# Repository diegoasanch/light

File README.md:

# Light

A WiFi-enabled LED light controller, based on the [RP2350](https://www.raspberrypi.com/products/rp2350/).

You can view the [PCB and schematics online here](https://kicanvas.org/?github=https://github.com/diegoasanch/light/blob/main/v1/kicad/light.kicad_pro).

<div align="center">

</div>

## What you'll see here

| File type                                     | Status        |
| --------------------------------------------- | -----------   |
| KiCad design files for the schematics and PCB | ✅             |
| Firmware source code                          | 🏗️ in progress |
| Interactive 3D PCB viewer (`web/`)            | ✅             |
| Frontend source code                          | -             |
| 3D models for the enclosure                   | -             |

> [!WARNING]
> This project is still under development.

## Why

I'm currently leveling up my electronics skills and learning about PCB design; I did a [similar (albeit much more simple) project](https://github.com/diegoasanch/RGB-Controller) in the past, so since I'm already familiar with the concepts I thought it would be a good starter project into the world of PCBs.

---

# Project structre

<div align="center">
  
</div>

## PCB

KiCad project, located in `./v1/kicad/` contains all of the designs and BOM

## Firmware

Cargo project using embassy-rs `./v1/firmware/`

## Web viewer

Interactive three.js render of the board built from the real KiCad data —
every copper layer, dielectric slab, mask, silkscreen and via as separate
toggleable 3D elements, with an exploded view. Lives in `./web/`
(`pnpm dev`); regenerate its data from the board file with `pnpm sync-pcb`.

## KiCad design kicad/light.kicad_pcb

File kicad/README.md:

# Configuring KiCad

No configuration needed: all project symbols, footprints and 3D models live in
`kicad/libs/` and are referenced via the built-in `${KIPRJMOD}` variable
(the directory containing the project file), so a fresh clone renders the full
3D board out of the box.

> Historical note: the project previously required a manually configured
> `LIGHT_PROJECT_LIB_DIR` path variable (`Preferences > Configure Paths...`).
> That was replaced with `${KIPRJMOD}/libs` in 2026-08 — if your KiCad still
> has the old variable defined, it is unused and can be deleted.

Stock-library models are referenced through `${KICAD9_3DMODEL_DIR}`; KiCad 10
resolves the legacy variable to its own model directory automatically (the
`.wrl` references resolve to the shipped `.step` files).

## 3D model sources

- `libs/RP2350_KiCad/` — symbol, footprint and STEP for the RP2350A from
  [HDR/RP2350_KiCad](https://github.com/HDR/RP2350_KiCad) (GPL-3.0, LICENSE
  included in the directory).
- `libs/GT-EVA01AA-L1.pretty/` — rotary encoder (G-Switch GT-EVA01AA-L1,
  LCSC C17702124) WRL/STEP fetched from the EasyEDA parts API via
  `easyeda2kicad`. The WRL is referenced by the board; the same-basename STEP
  is there for `kicad-cli pcb export step/glb --subst-models`. The raw
  EasyEDA STEP sits 0.9741 mm off the WRL in Y, so the committed STEP has the
  origin of its root `AXIS2_PLACEMENT_3D` (entity `#15348`) shifted by that
  amount — shifting the `CARTESIAN_POINT`s instead gets applied twice by the
  OCC import chain, and any edit must round-trip the file byte-exactly
  (an earlier encoding-damaged copy made OCC import it as empty geometry).
  Verified via `web/scripts/sync-pcb.ts`'s GLB export: model bbox center
  lands on the footprint to <0.1 µm.
- `DEBUG` (J8) and `GPIO` (J9) headers are marked DNP, so the 3D viewer hides
  their models unless "Models marked DNP" is enabled — this is intentional.

## PCB 3D Viewer

Colors matching the fabbed boards (blue mask, white silk, ENIG) are encoded in
two places:

- **Board stackup** (Board Setup → Physical Stackup, checked into this repo):
  solder mask `rgba(8, 72, 155, 0.902)`, silkscreen `White`, finish `ENIG`.
  Tick "Use board stackup colors" in the 3D viewer to use them. Note:
  `kicad-cli pcb render --use-board-stackup-colors` is broken in KiCad 10.0.5
  (renders the mask black even for stock templates) — use the preset below for
  CLI renders.
- **"fab blue" 3D viewer preset** (machine-local, in KiCad's `3d_viewer.json`):
  soldermask `rgba(8, 72, 155, 0.902)`, silkscreen `rgb(245, 245, 245)`,
  board body `rgba(30, 33, 32, 0.902)`, copper `rgb(191, 156, 59)`.
  Recreate it via 3D viewer → Appearance → save preset if on a new machine.

Render like the fab:

```bash
kicad-cli pcb render --preset "fab blue" --quality high -w 1920 -h 1440 --side top --background opaque --output render.png kicad/light.kicad_pcb
```

(The old manual note — board color #0A244A @ 95% — predates the fabbed boards
and is superseded by the values above, which were matched against photos of
the assembled rev with the blue JLC mask.)

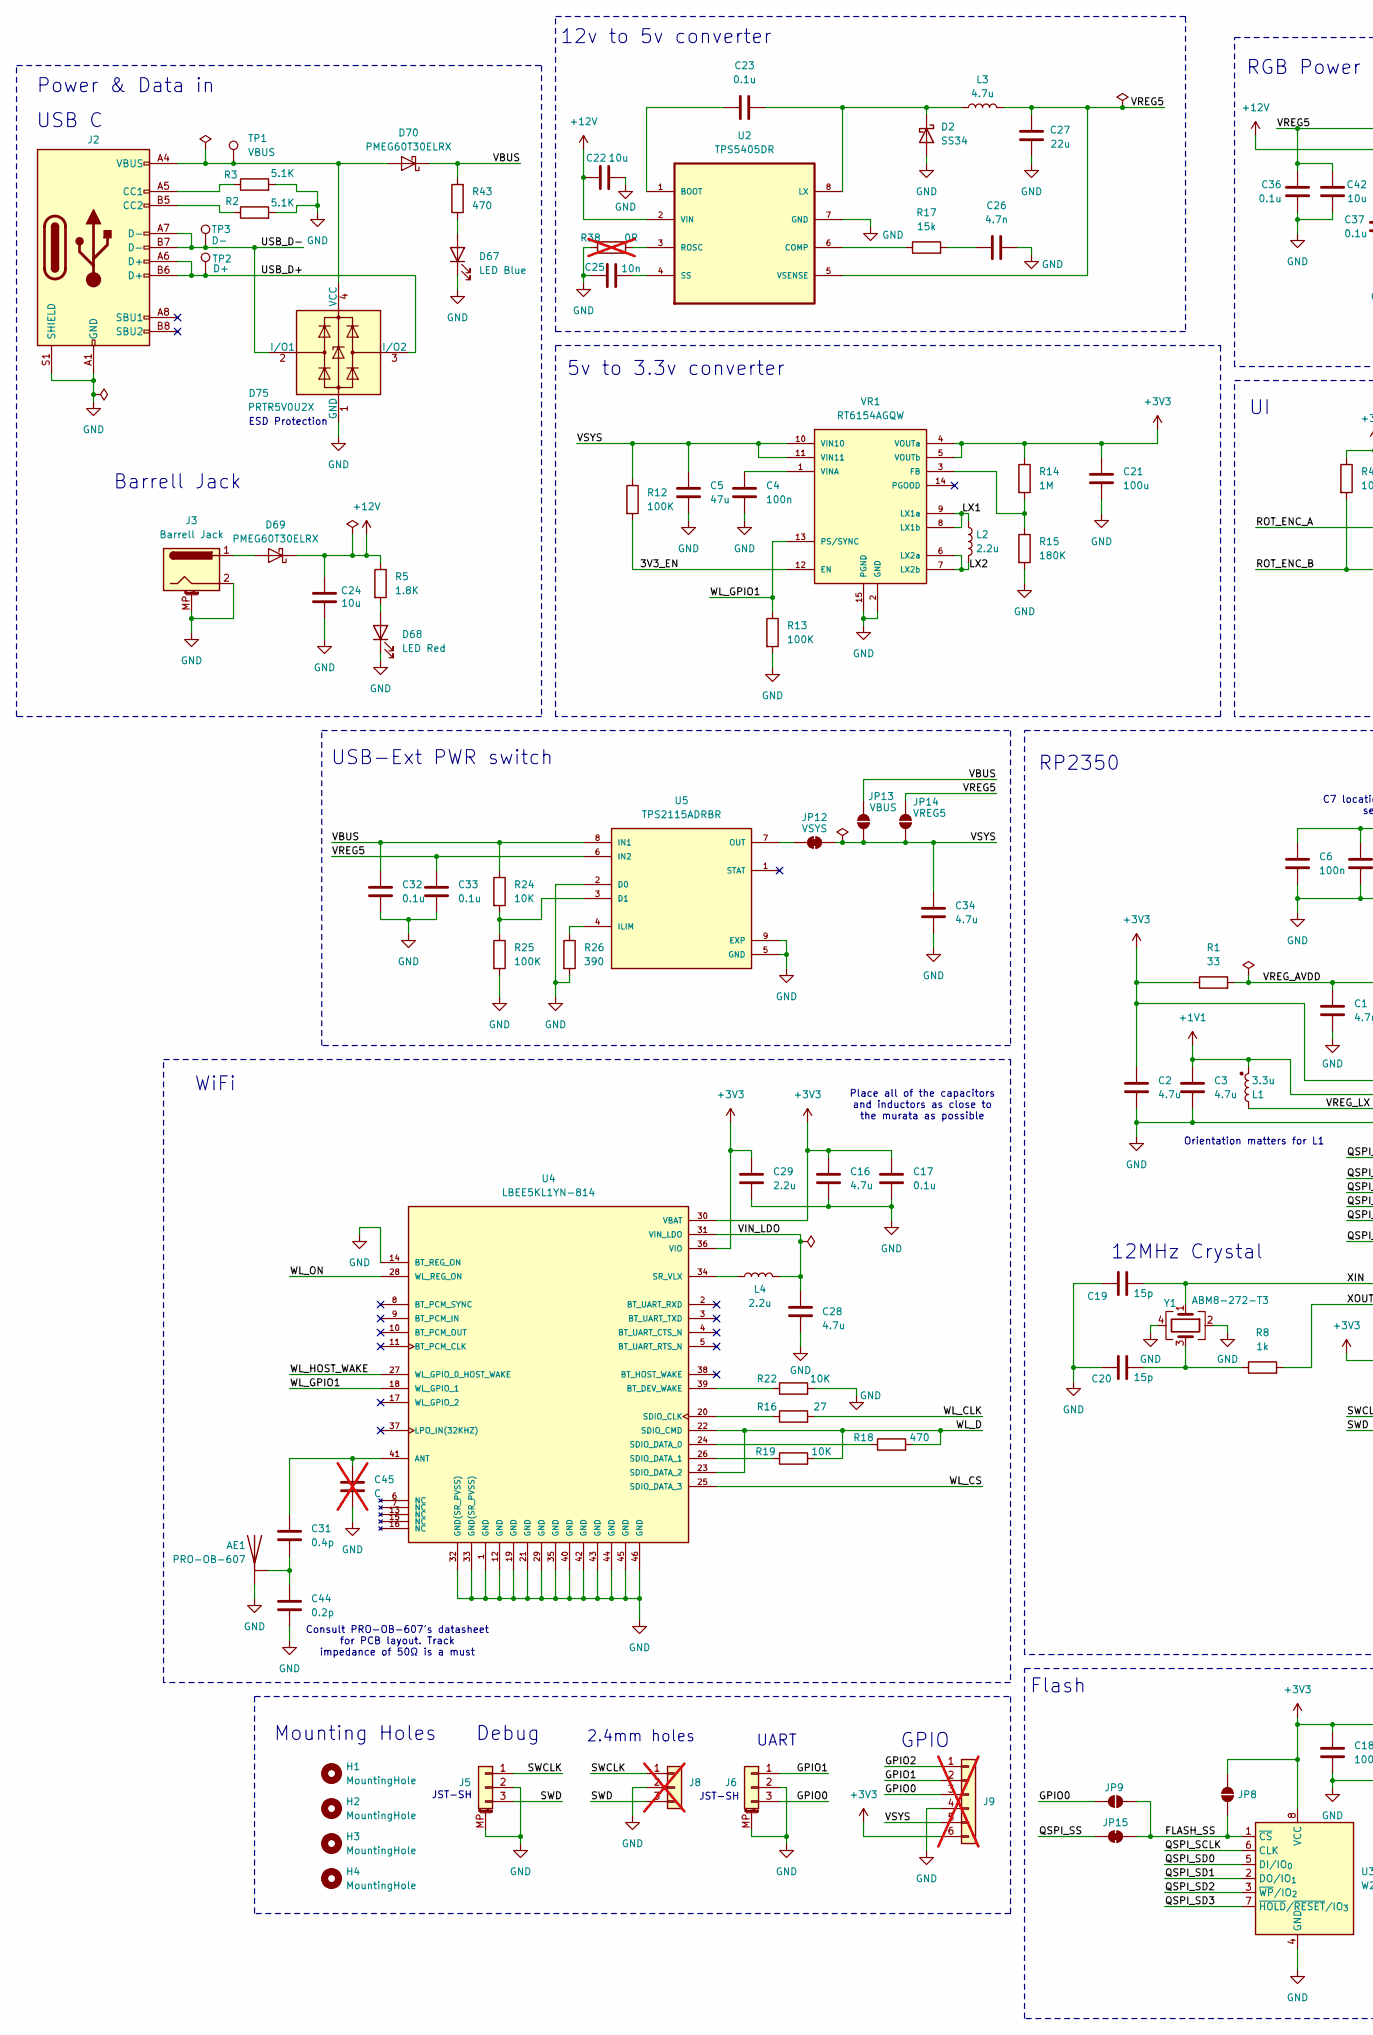
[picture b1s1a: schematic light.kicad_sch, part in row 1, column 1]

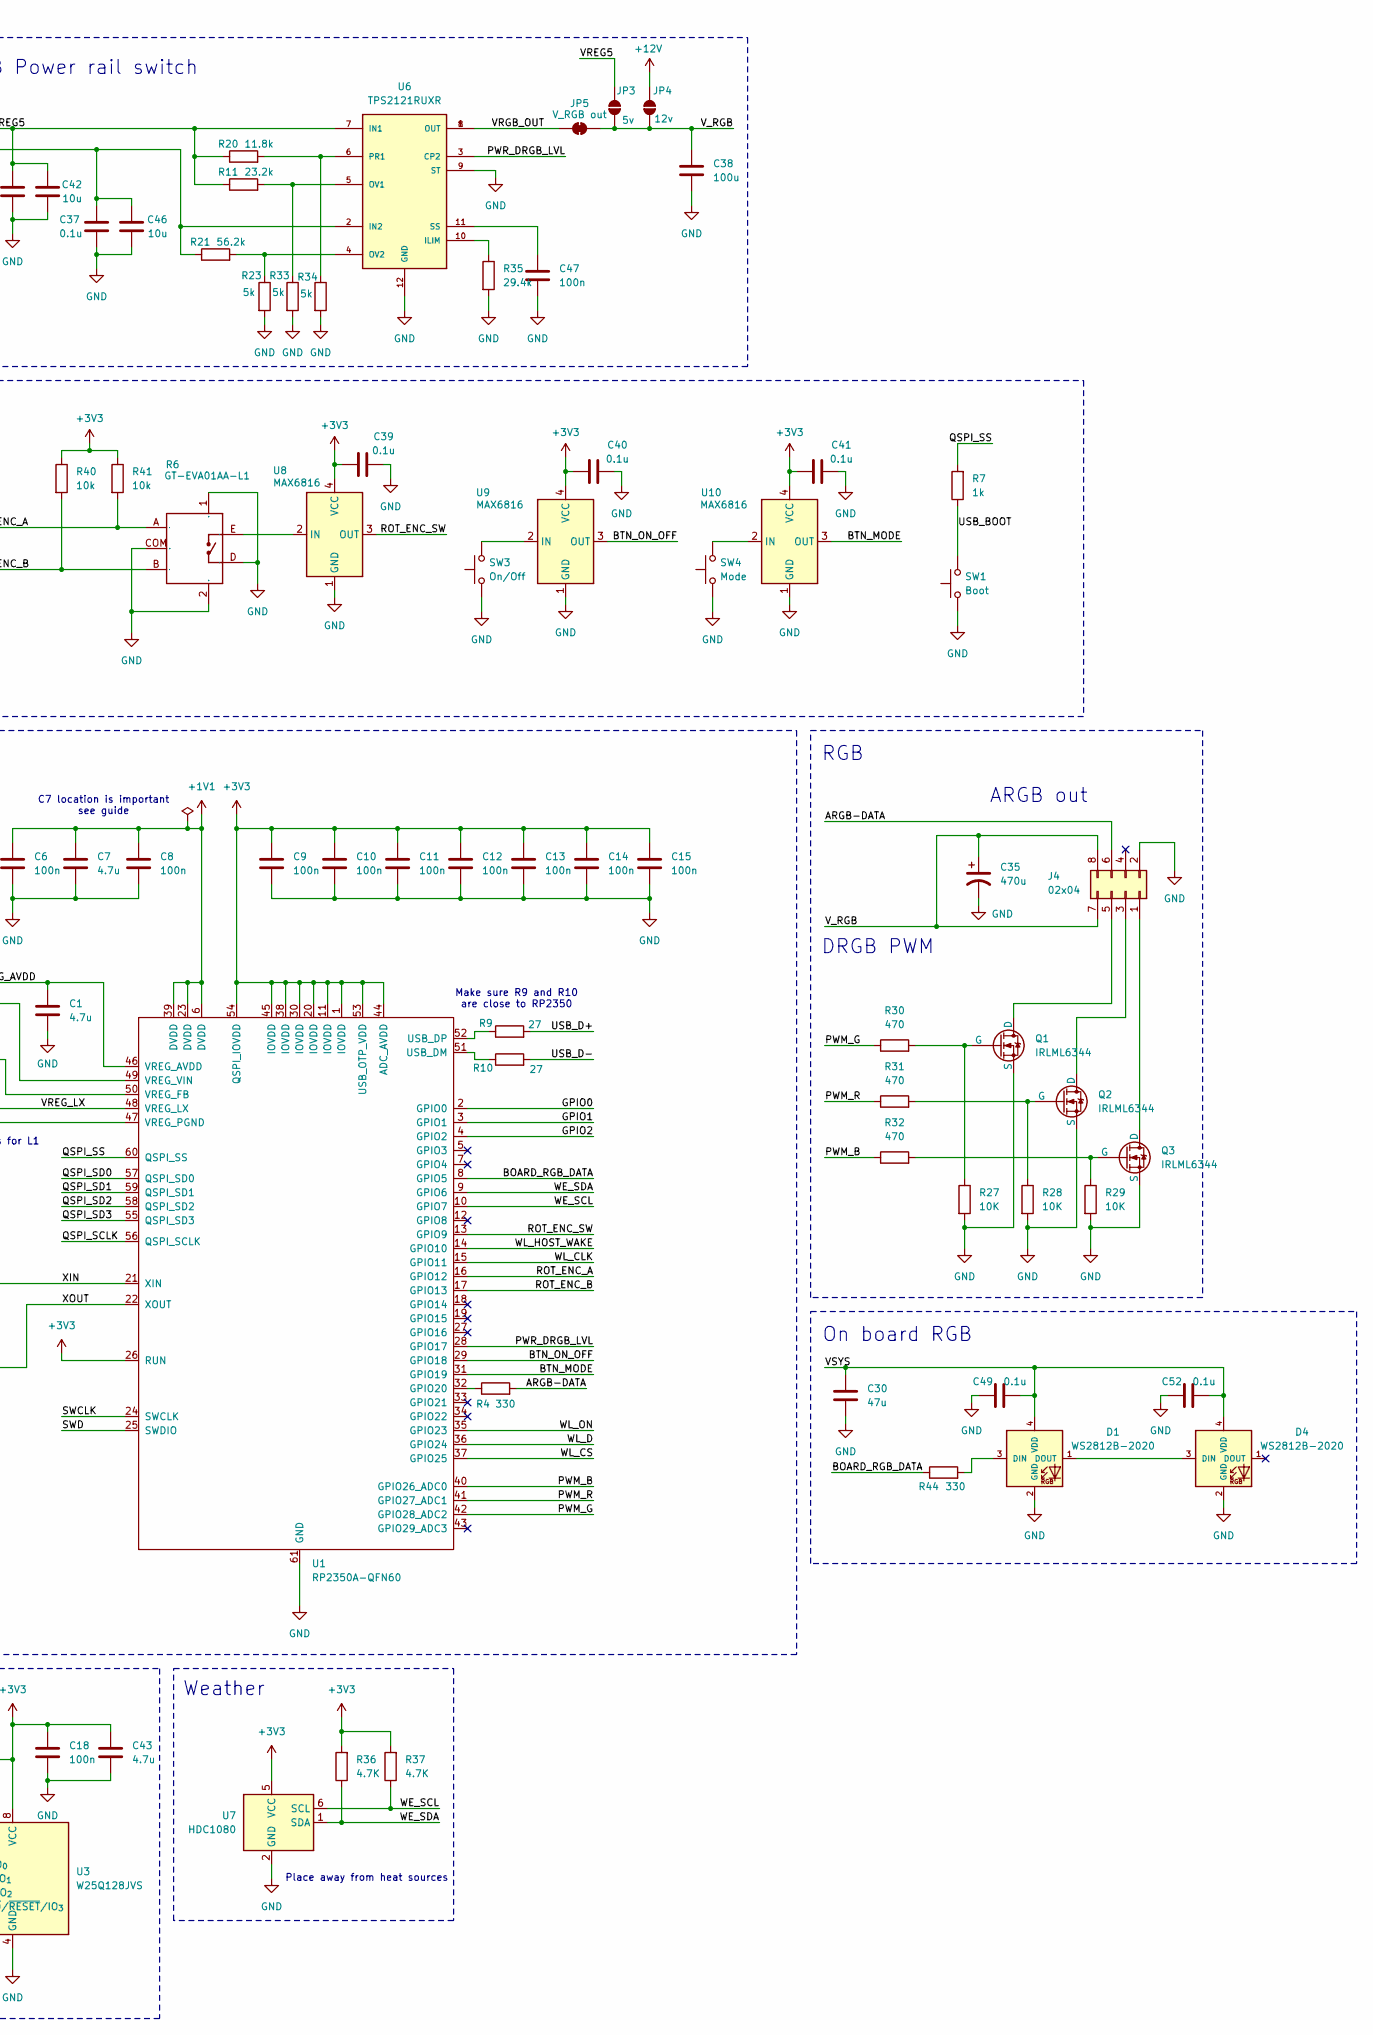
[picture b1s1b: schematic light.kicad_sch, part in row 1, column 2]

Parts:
AE1: PRO-OB-607; JLC C3284478
C1, C2, C3, C7, C43: 4.7u; C_0402_1005Metric; JLC C23733
C4, C6, C8, C9, C10, C11, C12, C13, C14, C15, C18: 100n; C_0201_0603Metric; JLC C76928
C5: 47u; C_0805_2012Metric; JLC C16780
C16, C28: 4.7u; C_0201_0603Metric; JLC C335103
C17, C23, C32, C33, C36, C37, C39, C40, C41, C49, C52: 0.1u; C_0201_0603Metric; JLC C76937
C19, C20: 15p; C_0201_0603Metric; JLC C161373
C21, C38: 100u; C_0805_2012Metric; JLC C141660
C22, C42, C46: 10u; C_0402_1005Metric; JLC C15525
C24: 10u; C_0603_1608Metric; JLC C96446
C25: 10n; C_0402_1005Metric; JLC C15195
C26: 4.7n; C_0402_1005Metric; JLC C1538
C27: 22u; C_0805_2012Metric; JLC C5674
C29: 2.2u; C_0201_0603Metric; JLC C76933
C30: 47u; C_0603_1608Metric; JLC C140782
C31: 0.4p; C_0402_1005Metric; JLC C20617855
C34: 4.7u; C_0603_1608Metric; JLC C19666
C35: 470u; CP_Elec_6.3x7.7; JLC C2977552
C44: 0.2p; C_0402_1005Metric; JLC C76908
C45: C; C_0402_1005Metric; not fitted
C47: 100n; C_0402_1005Metric; JLC C1525
D1, D4: WS2812B-2020; WS2812C-2020; JLC C965555
D2: SS34; SS24; JLC C8678
D67: LED Blue; LED_0603_1608Metric; JLC C7371904
D68: LED Red; LED_0603_1608Metric; JLC C7371906
D69, D70: PMEG60T30ELRX; Nexperia_CFP3_SOD-123W; JLC C2938304
D75: PRTR5V0U2X; SOT-143; JLC C12333
H1, H2, H3, H4: MountingHole; MountingHole_1.6mm
J2: USB_C_Receptacle_USB2.0_16P; USB_C_Receptacle_GCT_USB4105-xx-A_16P_TopMnt_Horizontal; JLC C2765186
J3: Barrell Jack; BarrelJack_GCT_DCJ200-10-A_Horizontal; JLC C720558
J4: 02x04; PinSocket_2x04_P2.54mm_Horizontal; JLC C2883572
J5, J6: SM03B-SRSS-TB; JST_SH_SM03B-SRSS-TB_1x03-1MP_P1.00mm_Horizontal; JLC C160403
J8: PinSocket_1x03_P2.54mm_Vertical; not fitted
J9: Conn_01x09_MountingPin; PinHeader_1x06_P2.54mm_Vertical; not fitted
JP3: 5v; SolderJumper-2_P1.3mm_Open_RoundedPad1.0x1.5mm
JP4: 12v; SolderJumper-2_P1.3mm_Open_RoundedPad1.0x1.5mm
JP5: V_RGB out; SolderJumper-2_P1.3mm_Bridged_RoundedPad1.0x1.5mm
JP8, JP9: SolderJumper_2_Open; SolderJumper-2_P1.3mm_Open_RoundedPad1.0x1.5mm
JP12: VSYS; SolderJumper-2_P1.3mm_Bridged_RoundedPad1.0x1.5mm
JP13: VBUS; SolderJumper-2_P1.3mm_Open_RoundedPad1.0x1.5mm
JP14: VREG5; SolderJumper-2_P1.3mm_Open_RoundedPad1.0x1.5mm
JP15: SolderJumper_2_Bridged; SolderJumper-2_P1.3mm_Bridged_RoundedPad1.0x1.5mm
L1: 3.3u; AOTA-B201610S3R3-101-T; JLC C42411119
L2: 2.2u; NRS5024T2R2NMGJ; JLC C222926
L3: 4.7u; LQH5BPZ4R7NT0L_5x5mm; JLC C703747
L4: 2.2u; L_0603_1608Metric; MFR.Part # LQM18PN2R2MGH; JLC C324471
Q1, Q2, Q3: IRLML6344; SOT-23; JLC C53550
R1: 33; R_0201_0603Metric; JLC C142009
R2, R3: 5.1K; R_0201_0603Metric; JLC C274341
R4: 330; R_0201_0603Metric; JLC C274872
R5: 1.8K; R_0402_1005Metric; JLC C25871
R6: GT-EVA01AA-L1; Manufacturer Part GT-EVA01AA-L1; JLC C17702124
R7: 1k; R_0402_1005Metric; JLC C11702
R8: 1k; R_0201_0603Metric; JLC C270365
R9, R10: 27; R_0201_0603Metric; JLC C473051
R11: 23.2k; R_0201_0603Metric; JLC C423655
R12: 100K; R_0402_1005Metric_Pad0.72x0.64mm_HandSolder; JLC C25741
R13: 100K; R_0201_0603Metric; JLC C270364
R14: 1M; R_0201_0603Metric; JLC C295786
R15: 180K; R_0201_0603Metric; JLC C295779
R16: 27; R_0402_1005Metric; JLC C138021
R17: 15k; R_0402_1005Metric; JLC C25756
R18, R30, R31, R32, R43: 470; R_0402_1005Metric; JLC C25117
R19, R22, R24, R27, R28, R29: 10K; R_0402_1005Metric; JLC C25744
R20: 11.8k; R_0201_0603Metric; JLC C2612393
R21: 56.2k; R_0201_0603Metric; JLC C226583
R23, R33, R34: 5k; R_0201_0603Metric; JLC C1857713
R25: 100K; R_0402_1005Metric; JLC C25741
R26: 390; R_0402_1005Metric; JLC C25109
R35: 29.4k; R_0402_1005Metric; JLC C5203996
R36, R37: 4.7K; R_0201_0603Metric; JLC C270346
R38: 0R; R_0603_1608Metric; not fitted
R40, R41: 10k; R_0402_1005Metric; JLC C25744
R44: 330; R_0402_1005Metric; JLC C25104
SW1: Boot; SW_SPST_B3U-1000P; JLC C843684
SW3: On/Off; SW_SPST_TL3342; JLC C2886897
SW4: Mode; SW_SPST_TL3342; JLC C2886897
TP1: VBUS; TestPoint_Pad_D1.0mm
TP2: D+; TestPoint_Pad_D1.0mm
TP3: D-; TestPoint_Pad_D1.0mm
U1: RP2350A-QFN60; RP2350A_QFN-60_EP_7.75x7.75_Pitch0.4mm; JLC C42411118
U2: TPS5405DR; SOIC127P599X175-8N; JLC C488409
U3: W25Q128JVS; SOIC-8_5.3x5.3mm_P1.27mm; JLC C97521
U4: LBEE5KL1YN-814; XCVR_LBEE5KL1YN-814; PARTREV C; JLC C6583742
U5: TPS2115ADRBR; SON65P300X300X100-9N; JLC C140321
U6: TPS2121RUXR; DigiKey_Part_Number 296-53410-1-ND
U7: HDC1080; HDC1080DMBT; JLC C82227
U8, U9, U10: MAX6816; SOT-143; JLC C41637
VR1: RT6154AGQW; VREG_RT6154AGQW; PARTREV 03; JLC C250400
Y1: ABM8-272-T3; Crystal_SMD_Abracon_ABM8G-4Pin_3.2x2.5mm; JLC C20625731

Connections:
+1V1: C3.1, C6.1, C7.1, C8.1, L1.2, U1.6 (DVDD), U1.23 (DVDD), U1.39 (DVDD), U1.50 (VREG_FB)
+3V3: C2.1, C9.1, C10.1, C11.1, C12.1, C13.1, C14.1, C15.1, C16.1, C17.1, C18.1, C21.1, C29.1, C39.1, C40.1, C41.1, C43.1, J9.6, JP8.2 (B), R1.1, R14.1, R36.2, R37.2, R40.1, R41.1, U1.1 (IOVDD), U1.11 (IOVDD), U1.20 (IOVDD), U1.26 (RUN), U1.30 (IOVDD), U1.38 (IOVDD), U1.44 (ADC_AVDD), U1.45 (IOVDD), U1.49 (VREG_VIN), U1.53 (USB_OTP_VDD), U1.54 (QSPI_IOVDD), U3.8 (VCC), U4.30 (VBAT), U4.36 (VIO), U7.5 (VCC), U8.4 (VCC), U9.4 (VCC), U10.4 (VCC), VR1.4 (VOUTa), VR1.5 (VOUTb)
+12V: C22.1, C24.2, C37.1, C46.1, D69.1 (K), JP4.2 (B), R5.1, R21.1, U2.2 (VIN), U6.2 (IN2)
/3V3_EN: R12.2, VR1.12 (EN)
/ARGB-DATA: J4.6 (Pin_4), R4.2
/BOARD_RGB_DATA: R44.1, U1.8 (GPIO5)
/BTN_MODE: U1.31 (GPIO19), U10.3 (OUT)
/BTN_ON_OFF: U1.29 (GPIO18), U9.3 (OUT)
/FLASH_SS: JP8.1 (A), JP9.1 (A), JP15.2 (B), U3.1 (~CS)
/GPIO0: J6.3, J9.3, JP9.2 (B), U1.2 (GPIO0)
/GPIO1: J6.1, J9.2, U1.3 (GPIO1)
/GPIO2: J9.1, U1.4 (GPIO2)
/LX1: L2.1, VR1.8 (LX1b), VR1.9 (LX1a)
/LX2: L2.2, VR1.6 (LX2a), VR1.7 (LX2b)
/PWM_B: R32.1, U1.40 (GPIO26_ADC0)
/PWM_G: R30.1, U1.42 (GPIO28_ADC2)
/PWM_R: R31.1, U1.41 (GPIO27_ADC1)
/PWR_DRGB_LVL: U1.28 (GPIO17), U6.3 (CP2)
/QSPI_SCLK: U1.56 (QSPI_SCLK), U3.6 (CLK)
/QSPI_SD0: U1.57 (QSPI_SD0), U3.5 (DI/IO_{0})
/QSPI_SD1: U1.59 (QSPI_SD1), U3.2 (DO/IO_{1})
/QSPI_SD2: U1.58 (QSPI_SD2), U3.3 (~WP/IO_{2})
/QSPI_SD3: U1.55 (QSPI_SD3), U3.7 (~HOLD/~RESET/IO_{3})
/QSPI_SS: JP15.1 (A), R7.2, U1.60 (QSPI_SS)
/ROT_ENC_A: R6.A, R41.2, U1.16 (GPIO12)
/ROT_ENC_B: R6.B, R40.2, U1.17 (GPIO13)
/ROT_ENC_SW: U1.13 (GPIO9), U8.3 (OUT)
/SWCLK: J5.1, J8.1, U1.24 (SWCLK)
/SWD: J5.3, J8.3, U1.25 (SWDIO)
/USB_BOOT: R7.1, SW1.2
/USB_D+: D75.3 (I/O2), J2.A6 (D+), J2.B6 (D+), R9.2, TP2.1
/USB_D-: D75.2 (I/O1), J2.A7 (D-), J2.B7 (D-), R10.2, TP3.1
/VBUS: C32.1, D70.1 (K), JP13.2 (B), R24.1, R43.2, U5.8 (IN1)
/VIN_LDO: C28.1, L4.2, U4.31 (VIN_LDO)
/VREG5: C27.1, C33.1, C36.1, C42.1, JP3.2 (B), JP14.2 (B), L3.2, R11.1, R20.1, U2.5 (VSENSE), U5.6 (IN2), U6.7 (IN1)
/VREG_AVDD: C1.1, R1.2, U1.46 (VREG_AVDD)
/VREG_LX: L1.1, U1.48 (VREG_LX)
/VRGB_OUT: JP5.1 (A), U6.1 (OUT), U6.8 (OUT)
/VSYS: C5.1, C30.1, C34.1, C49.2, C52.2, D1.4 (VDD), D4.4 (VDD), J9.5, JP12.2 (B), JP13.1 (A), JP14.1 (A), R12.1, VR1.10 (VIN10), VR1.11 (VIN11)
/V_RGB: C35.1, C38.1, J4.7 (Pin_1), J4.8 (Pin_2), JP3.1 (A), JP4.1 (A), JP5.2 (B)
/WE_SCL: R37.1, U1.10 (GPIO7), U7.6 (SCL)
/WE_SDA: R36.1, U1.9 (GPIO6), U7.1 (SDA)
/WL_CLK: R16.2, U1.15 (GPIO11)
/WL_CS: U1.37 (GPIO25), U4.25 (SDIO_DATA_3)
/WL_D: R18.2, R19.2, U1.36 (GPIO24), U4.22 (SDIO_CMD), U4.23 (SDIO_DATA_2)
/WL_GPIO1: R13.1, U4.18 (WL_GPIO_1), VR1.13 (PS/SYNC)
/WL_HOST_WAKE: U1.14 (GPIO10), U4.27 (WL_GPIO_0_HOST_WAKE)
/WL_ON: U1.35 (GPIO23), U4.28 (WL_REG_ON)
/XIN: C19.2, U1.21 (XIN), Y1.1
/XOUT: R8.2, U1.22 (XOUT)
GND: AE1.1 (GND), C1.2, C2.2, C3.2, C4.2, C5.2, C6.2, C7.2, C8.2, C9.2, C10.2, C11.2, C12.2, C13.2, C14.2, C15.2, C16.2, C17.2, C18.2, C19.1, C20.1, C21.2, C22.2, C24.1, C25.2, C26.2, C27.2, C28.2, C29.2, C30.2, C32.2, C33.2, C34.2, C35.2, C36.2, C37.2, C38.2, C39.2, C40.2, C41.2, C42.2, C43.2, C44.2, C45.2, C46.2, C47.2, C49.1, C52.1, D1.2 (GND), D2.2 (A), D4.2 (GND), D67.1 (K), D68.1 (K), D75.1 (GND), J2.A1 (GND), J2.A12 (GND), J2.B1 (GND), J2.B12 (GND), J2.S1 (SHIELD), J3.2, J3.MP (MountPin), J4.2 (Pin_8), J5.2, J5.MP (MountPin), J6.2, J6.MP (MountPin), J8.2, J9.4, Q1.3 (S), Q2.3 (S), Q3.3 (S), R2.2, R3.2, R6.1 (MP1), R6.2 (MP2), R6.COM, R6.D, R13.2, R15.2, R22.2, R23.2, R25.2, R26.2, R27.2, R28.2, R29.2, R33.2, R34.2, R35.2, R38.1, SW1.1, SW3.1, SW4.1, U1.47 (VREG_PGND), U1.61 (GND), U2.7 (GND), U3.4 (GND), U4.1 (GND), U4.12 (GND), U4.14 (BT_REG_ON), U4.19 (GND), U4.21 (GND), U4.29 (GND), U4.32 (GND(SR_PVSS)), U4.33 (GND(SR_PVSS)), U4.35 (GND), U4.40 (GND), U4.42 (GND), U4.43 (GND), U4.44 (GND), U4.45 (GND), U4.46 (GND), U5.2 (D0), U5.5 (GND), U5.9 (EXP), U6.9 (ST), U6.12 (GND), U7.2 (GND), U8.1 (GND), U9.1 (GND), U10.1 (GND), VR1.2 (GND), VR1.15 (PGND), Y1.2, Y1.4
unnamed: AE1.2 (RF_Feed), C31.2, C44.1
unnamed: C20.2, R8.1, Y1.3
unnamed: C26.1, R17.2
unnamed: D1.3 (DIN), R44.2
unnamed: D1.1 (DOUT), D4.3 (DIN)
unnamed: C23.2, D2.1 (K), L3.1, U2.8 (LX)
unnamed: D67.2 (A), R43.1
unnamed: D68.2 (A), R5.2
unnamed: D69.2 (A), J3.1
unnamed: D70.2 (A), D75.4 (VCC), J2.A4 (VBUS), J2.A9 (VBUS), J2.B4 (VBUS), J2.B9 (VBUS), TP1.1
unnamed: J2.A5 (CC1), R3.1
unnamed: J2.B5 (CC2), R2.1
unnamed: J4.5 (Pin_3), Q1.1 (D)
unnamed: J4.3 (Pin_5), Q2.1 (D)
unnamed: J4.1 (Pin_7), Q3.1 (D)
unnamed: JP12.1 (A), U5.7 (OUT)
unnamed: Q1.2 (G), R27.1, R30.2
unnamed: Q2.2 (G), R28.1, R31.2
unnamed: Q3.2 (G), R29.1, R32.2
unnamed: R4.1, U1.32 (GPIO20)
unnamed: R10.1, U1.51 (USB_DM)
unnamed: R9.1, U1.52 (USB_DP)
unnamed: C23.1, U2.1 (BOOT)
unnamed: R17.1, U2.6 (COMP)
unnamed: R38.2, U2.3 (ROSC)
unnamed: C25.1, U2.4 (SS)
unnamed: C31.1, C45.1, U4.41 (ANT)
unnamed: R22.1, U4.39 (BT_DEV_WAKE)
unnamed: R16.1, U4.20 (SDIO_CLK)
unnamed: R18.1, U4.24 (SDIO_DATA_0)
unnamed: R19.1, U4.26 (SDIO_DATA_1)
unnamed: L4.1, U4.34 (SR_VLX)
unnamed: R24.2, R25.1, U5.3 (D1)
unnamed: R26.1, U5.4 (ILIM)
unnamed: R35.1, U6.10 (ILIM)
unnamed: R11.2, R33.1, U6.5 (OV1)
unnamed: R21.2, R23.1, U6.4 (OV2)
unnamed: R20.2, R34.1, U6.6 (PR1)
unnamed: C47.1, U6.11 (SS)
unnamed: R6.E, U8.2 (IN)
unnamed: SW3.2, U9.2 (IN)
unnamed: SW4.2, U10.2 (IN)
unnamed: R14.2, R15.1, VR1.3 (FB)
unnamed: C4.1, VR1.1 (VINA)

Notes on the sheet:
ESD Protection
Mounting Holes
Place all of the capacitors and inductors as close to the murata as possible
2.4mm holes
Place away from heat sources
ARGB out
Make sure R9 and R10 are close to RP2350
Weather
USB C
RGB
Orientation matters for L1
Barrell Jack
C7 location is important see guide
GPIO
UART
Consult PRO-OB-607's datasheet for PCB layout. Track impedance of 50Ω is a must
12v to 5v converter
Flash
DRGB PWM
5v to 3.3v converter
USB-Ext PWR switch
RGB Power rail switch
RP2350
12MHz Crystal
On board RGB
WiFi
Debug
JST-SH
Power & Data in

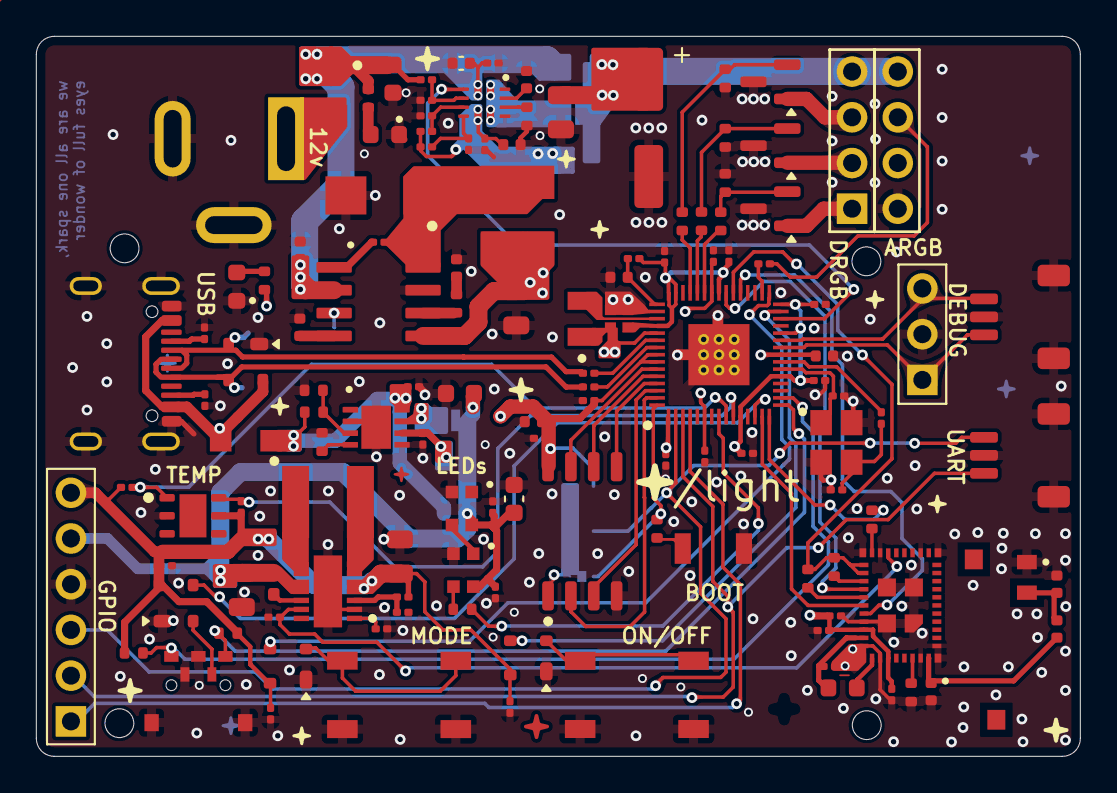
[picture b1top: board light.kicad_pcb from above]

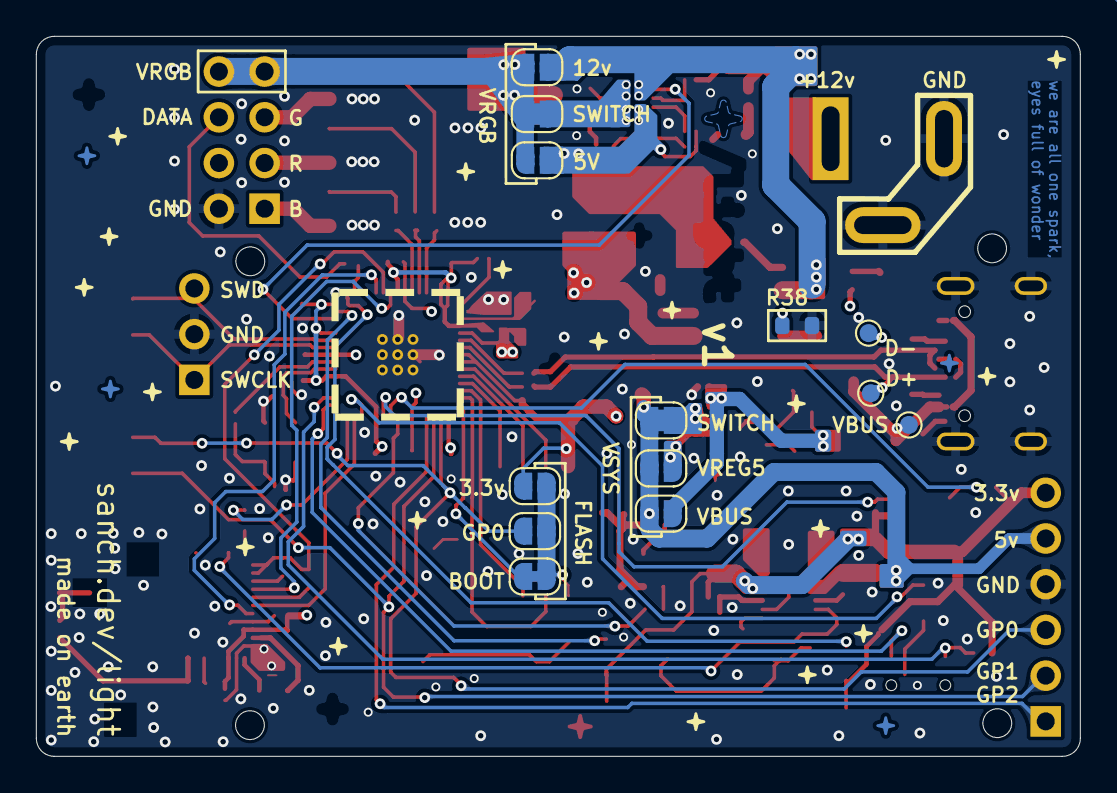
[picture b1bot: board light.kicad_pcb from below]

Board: 4 copper layers, 58.0 x 40.0 mm, 145 parts (13 on the bottom side), 95 nets.

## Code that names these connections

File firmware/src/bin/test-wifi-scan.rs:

//! WiFi bring-up test: detect the CYW43439 (Murata 1YN module) and scan for networks.
//!
//! This is the FIRST binary to run when validating WiFi on the board — it needs no
//! credentials and exercises exactly the layers that can fail, in order:
//! bus detection (FEEDBEAD) → firmware load → radio up → scan.
//!
//! Full driver logging (cyw43/cyw43_pio at trace) is baked into
//! .cargo/config.toml — the detection stage only logs at trace level, and at
//! plain `debug` a dead bus is totally silent. So simply:
//!
//!     cargo run --release --bin test-wifi-scan
//!
//! Positive controls that the trace filter is really active (defmt filtering is
//! compile-time; run `cargo clean -p cyw43 -p cyw43-pio` if these are missing):
//! cyw43_pio prints its PIO-program/frequency choice at startup, and right
//! after STAGE 2 cyw43 traces "WL_REG off/on" then "read REG_BUS_TEST_RO".
//!
//! How to read the output:
//! - Hangs after "STAGE 2" with no cyw43 logs (at trace: endless REG_BUS_TEST_RO reads)
//!   → gSPI bus problem: chip not answering (pins/power/strap). Trace read values:
//!   constant 0x00000000 = no response (unpowered or strapped into SDIO mode);
//!   constant 0xFFFFFFFF = floating DIO; unstable garbage = clocking/signal integrity.
//! - "chip ID: 43439" then hang at "waiting for HT clock..." or an F2-ready timeout
//!   panic → firmware blob upload problem (or marginal bus corrupting bulk transfers —
//!   try halving the SPI clock before blaming blobs; ours are sha256-verified).
//! - Panic "timeout while waiting for alp clock!" → chip detected but sick bus/clock.
//! - STAGE 3 + scan results → WiFi hardware fully vindicated.
//!
//! Board pin map (netlist-verified against kicad/light.kicad_sch rev 5):
//!   WL_ON  (module WL_REG_ON) = GPIO23,  WL_CS (SDIO_DATA_3) = GPIO25
//!   WL_D   (SDIO_CMD+DATA_2, the gSPI DIO) = GPIO24
//!   WL_CLK (SDIO_CLK, via 27R)             = GPIO11   <- NOT GPIO29 like the Pico 2W!

#![no_std]
#![no_main]

use core::str;

use cyw43::aligned_bytes;
use cyw43_pio::{PioSpi, RM2_CLOCK_DIVIDER};
use defmt::*;
use embassy_executor::Spawner;
use embassy_rp::gpio::{Level, Output};
use embassy_rp::peripherals::{DMA_CH0, PIO0};
use embassy_rp::pio::{InterruptHandler, Pio};
use embassy_rp::{bind_interrupts, dma};
use embassy_time::{Duration, Timer};
use static_cell::StaticCell;
use {defmt_rtt as _, panic_probe as _};

bind_interrupts!(struct Irqs {
    PIO0_IRQ_0 => InterruptHandler<PIO0>;
    DMA_IRQ_0 => dma::InterruptHandler<DMA_CH0>;
});

#[embassy_executor::task]
async fn cyw43_task(
    runner: cyw43::Runner<'static, cyw43::SpiBus<Output<'static>, PioSpi<'static, PIO0, 0>>>,
) -> ! {
    runner.run().await
}

#[embassy_executor::main]
async fn main(spawner: Spawner) {
    info!("STAGE 0: booted, initializing peripherals");
    let p = embassy_rp::init(Default::default());

    // Real blobs, sha256-verified — see cyw43-firmware/README.md for provenance.
    let fw = aligned_bytes!("../../cyw43-firmware/43439A0.bin");
    let clm = aligned_bytes!("../../cyw43-firmware/43439A0_clm.bin");
    let nvram = aligned_bytes!("../../cyw43-firmware/nvram_rp2040.bin");

    let pwr = Output::new(p.PIN_23, Level::Low); // WL_ON -> module WL_REG_ON
    let cs = Output::new(p.PIN_25, Level::High); // WL_CS
    let mut pio = Pio::new(p.PIO0, Irqs);
    let spi = PioSpi::new(
        &mut pio.common,
        pio.sm0,
        // 25 MHz gSPI: the conservative bring-up divider the embassy examples use
        // (https://github.com/embassy-rs/embassy/issues/3960). With the 27R series
        // resistor in WL_CLK, don't chase higher speeds until everything works.
        RM2_CLOCK_DIVIDER,
        pio.irq0,
        cs,
        p.PIN_24, // dio = WL_D
        p.PIN_11, // clk = WL_CLK (board-specific; Pico 2W uses GPIO29 here)
        dma::Channel::new(p.DMA_CH0, Irqs),
    );
    info!("STAGE 1: PioSpi ready (DIO=GPIO24, CLK=GPIO11, CS=GPIO25) — DIO+CLK now driven low");

    static STATE: StaticCell<cyw43::State> = StaticCell::new();
    let state = STATE.init(cyw43::State::new());

    info!("STAGE 2: cyw43::new — toggling REG_ON (GPIO23), then FEEDBEAD detection poll...");
    let (_net_device, mut control, runner) = cyw43::new(state, pwr, spi, fw, nvram).await;
    info!("STAGE 3: chip detected and firmware+NVRAM loaded!");

    spawner.spawn(unwrap!(cyw43_task(runner)));

    control.init(clm).await;
    control
        .set_power_management(cyw43::PowerManagementMode::PowerSave)
        .await;
    info!("STAGE 4: CLM loaded, radio configured — scanning");

    loop {
        let mut scanner = control.scan(Default::default()).await;
        let mut count = 0u32;
        while let Some(bss) = scanner.next().await {
            count += 1;
            let ssid_len = (bss.ssid_len as usize).min(bss.ssid.len());
            match str::from_utf8(&bss.ssid[..ssid_len]) {
                Ok(ssid_str) => {
                    info!("  found AP: {} (bssid {:x}, rssi {})", ssid_str, bss.bssid, bss.rssi)
                }
                Err(_) => info!("  found AP: <non-utf8 ssid> (bssid {:x}, rssi {})", bss.bssid, bss.rssi),
            }
        }
        drop(scanner);
        info!("scan pass complete: {} APs — rescanning in 5s", count);
        Timer::after(Duration::from_secs(5)).await;
    }
}

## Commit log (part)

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2025-03-01 init project
2025-03-01 Diagram power on schematic
2025-03-01 Add flash to schematic
2025-03-02 Add crystal
2025-03-02 Finish minimal board
2025-03-02 Add new power supply
2025-03-03 Add barrel jack and power switch for protection
2025-03-05 Add wifi
2025-03-06 Add antenna
2025-03-06 Add 3D models to imported footprints
2025-03-06 Replace PMOS with TI TPS2115A power mux
2025-03-06 Add readme
2025-03-06 Create LICENSE
2025-03-06 reorganize schematic
2025-03-06 Add diagram to readme
2025-03-07 Add DRGB PWM and power switch
2025-03-08 Add some footprints
2025-03-11 add weather module
2025-03-12 Add buttons
2025-03-14 Add rotary encoder; cleanup
2025-03-21 Fix rotary encoder wiring; use the encoder switch
2025-03-22 add switch debouncers
2025-03-22 marked redundant pull up resistors as DNP
2025-03-23 add ARGB output
2025-03-23 Add PIR motion sensor
2025-03-23 add PIR lib locally
2025-03-23 bring all external symbols, footprints, and 3D models to the project's directory
2025-03-23 add kicad readme
2025-03-24 add ESD protection; fix matrix power rail; general cleanup; this commit marks the completion of the schematics milestone
2025-03-24 specify capacitor footprints
2025-03-24 fix 3d models
2025-03-24 reorganize layout
2025-03-26 add pull up resistors to rot enc a,b; add debug connector next to GPIO
2025-03-26 add gpio 4,5 and LED on 5
2025-03-26 beef up ESD protection
2025-03-26 selected some footprints; imported model for SS24 diode
2025-03-27 add some more footprints
2025-03-28 create RP Inductor footprint; add AOTA-B201610S3R3-101-T 3D model
2025-03-28 set inductors
2025-03-30 finish footprint selection
2025-03-30 fix wrong pin name on footprints
2025-03-30 import jlcpcb board settings
2025-03-30 group components
2025-03-30 general layout
2025-03-30 change rgb to 2x4 pins; general layout
2025-03-31 organize RP2350 group layout
2025-03-31 more layout
2025-04-03 remove reset btn; move layout
2025-04-04 remove RGB array
2025-04-04 remove RGB array; remove movement sensor; decrease number of exposed GPIOs; improve layout
2025-04-05 start routing
2025-04-06 route the RP power regulator
2025-04-06 route USB
2025-04-06 routing & routing & routing & routing &
2025-04-07 route wireless module
2025-04-07 finish routing
2025-04-07 tweak copper pour parameters; solve some DRC errors
2025-04-08 solve some DRC errors
2025-04-08 change readme URL to project view
2025-04-10 add mounting holes and fix isolated GND islands
2025-04-11 make corners rounded
2025-04-11 route antenna!!! oficially routed the hole board; also solved remaining DRC errors
2025-04-13 remove some silkscreen component outlines
2025-04-13 add silkscreen labels and graphics
2025-04-13 add review images
2025-04-17 create new footprint for mounting hole link it to a schematic symbol; solve DRC errors
2025-04-17 general stuff
2025-04-17 tweaks
2025-04-18 add rev 2 assets
2025-04-19 review stuff
2025-04-23 improve graphics
2025-05-02 add TPS2120 symbol, footprint, and 3D model
2025-05-13 replace the power switch with the TPS2120
2025-05-14 layout pwr switch on PCB
2025-06-20 checkpoint
2025-06-20 resolve DRC errors
2025-06-20 finish connections! resolve warnings
2025-06-20 rev 3
2025-08-10 x review
2025-08-10 routing improvements
2025-08-10 improve layout; increase space between components
2025-08-11 general layour improvements
2025-08-11 rev 5; replaced single RED LED with added 2x2 RGB LEDs
2025-08-14 shrink C27; layout improvements; prod is getting closer
2025-08-15 impedance matching ()yay)
2025-08-15 add some component codes
2025-08-15 power routing improvements
2025-08-16 component assignment
2025-08-16 routing improvements, took USB diff pair to the top plane no vias (as it should have been since the beginning); improve power delivery
2025-08-16 more component assignment
2025-08-16 mooooarr component ass ignment
2025-08-17 replace TPS2120 with TPS2121
2025-08-18 component validations
2025-08-18 style details; component assignment
2025-08-23 change LEDs 1010 → 2020; general improvements
2025-08-23 general improvements
2025-08-23 detailing
2025-08-23 fix inverted diode
2025-08-23 add teardrops to vias; fix D2's orientation
2025-08-24 okay we're ready
2025-08-29 backup sesh
2025-09-18 setup rust project
2025-09-18 improve readme, add LEDs test
2025-09-19 add pcb copper image
2025-09-20 add pcb color
2025-09-22 rename test files
2025-09-22 add power switch test
2025-09-22 extract RGB test logic into a new component
2025-09-26 add debug configuration
2025-09-26 add some cursor rules
2025-09-27 add rotary encoder module and test script
2025-09-27 make argb module generic; add external LEDs test script
2025-09-27 add test file for controlling external LED brightness using the rotary encoder
2025-09-28 Refactor rotary encoder to group fast edges into clusters
2025-09-29 Refactor rotary encoder cluster detection logic
2025-09-29 use select3 instead of nested selects
2025-09-29 Refactor rotary encoder clustering logic
    Simplify clustering to a fixed time window and majority vote.
2025-09-29 add threshold early returns
2025-09-29 cleanup
2025-09-29 replace \ Timer::after_millis` with `Ticker.next`; cleanup
2025-09-29 change readme images' order
